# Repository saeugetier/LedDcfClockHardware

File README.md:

# LedDcfClockHardware

The hardware used for https://github.com/saeugetier/LedDcfClock

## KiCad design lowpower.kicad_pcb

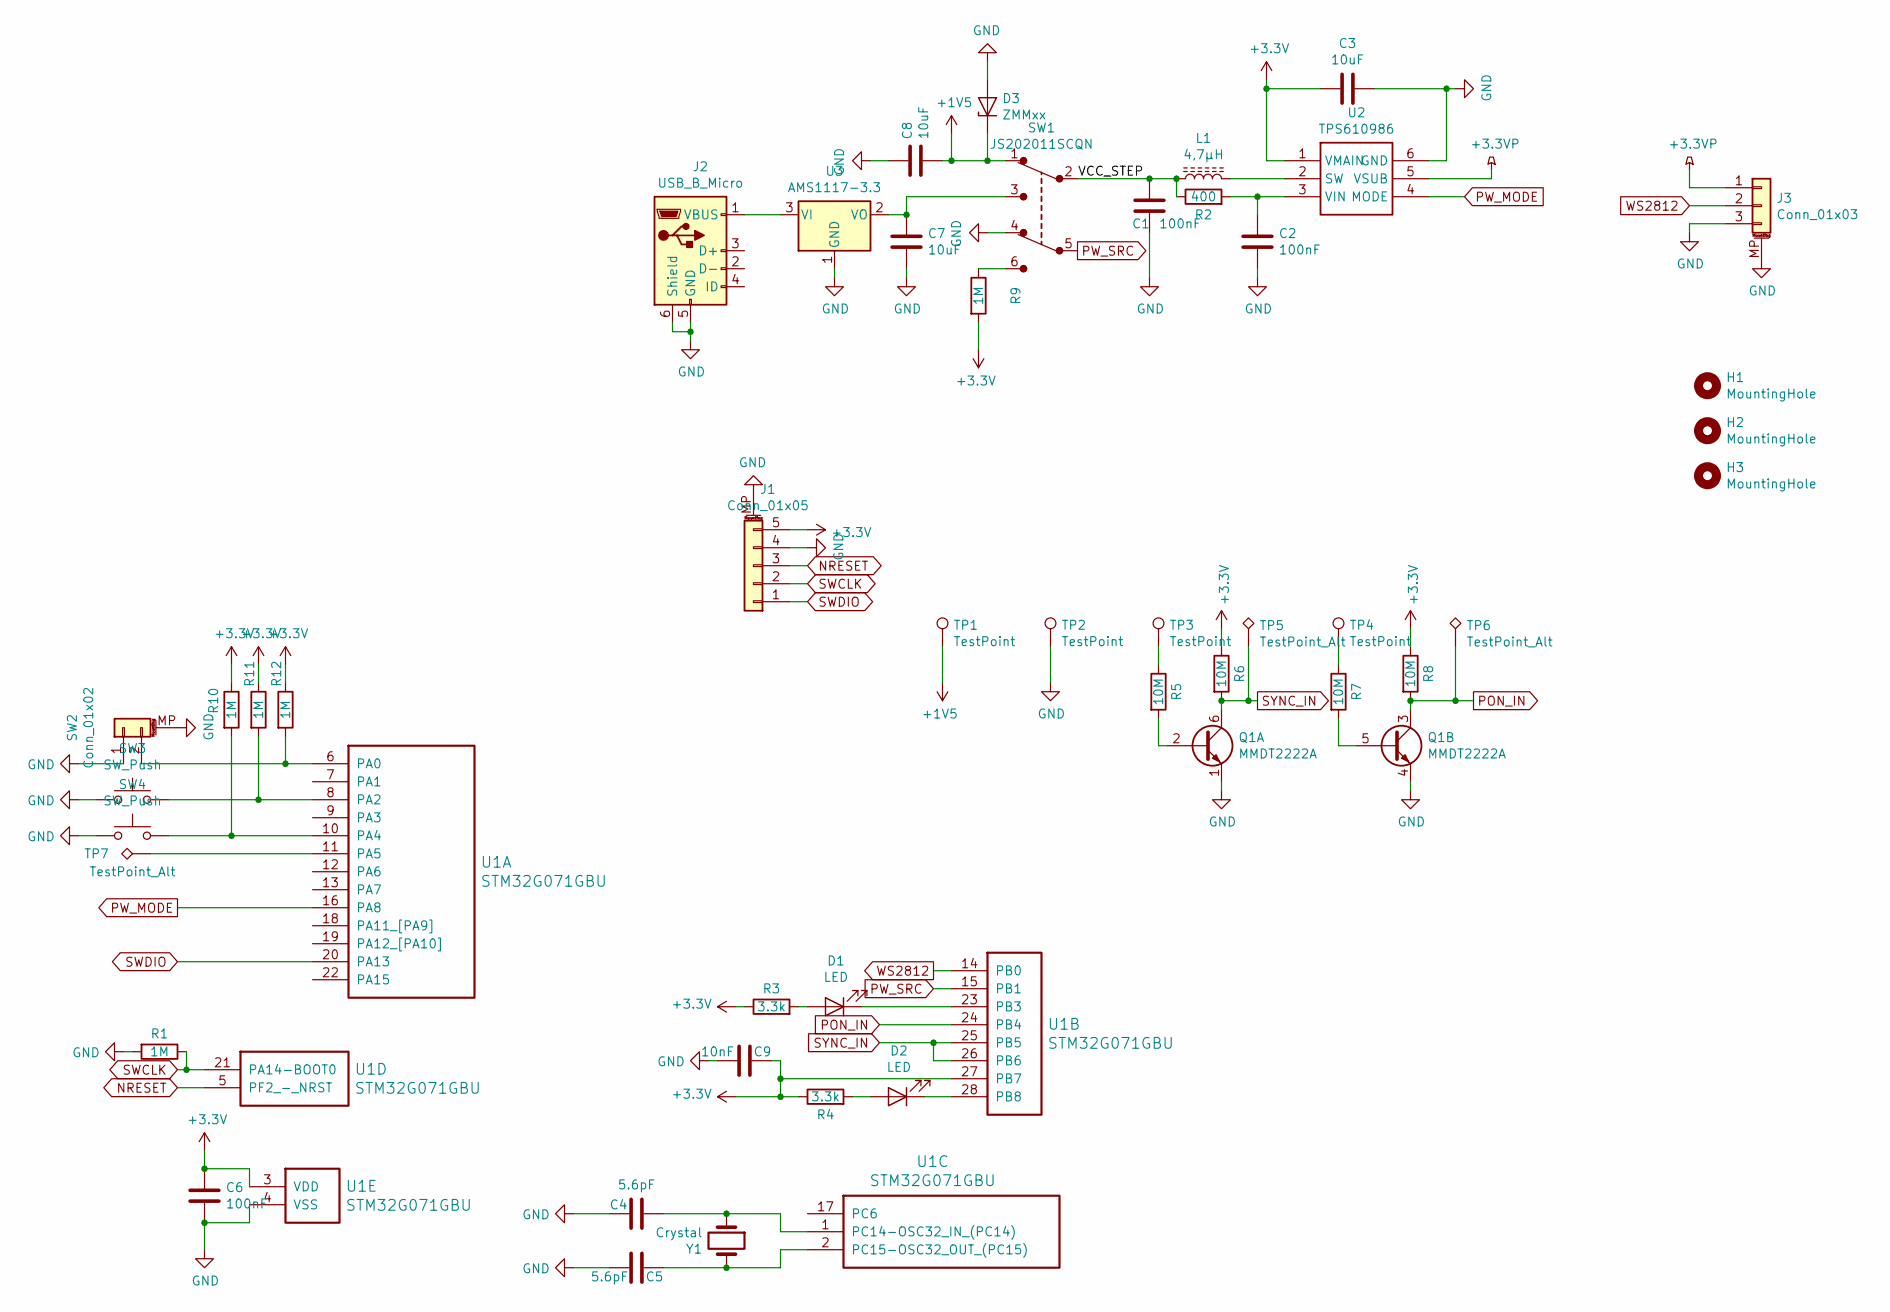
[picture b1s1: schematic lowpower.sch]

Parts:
C1, C2, C6: 100nF; C_0603_1608Metric
C3, C7, C8: 10uF; C_0603_1608Metric
C4, C5: 5.6pF; C_0603_1608Metric
C9: 10nF; C_0603_1608Metric
D1, D2: LED; LED_0603_1608Metric
D3: ZMMxx; D_MiniMELF
H1, H2, H3: MountingHole; MountingHole_3.2mm_M3_DIN965
J1: Conn_01x05; JST_SH_BM05B-SRSS-TB_1x05-1MP_P1.00mm_Vertical
J2: USB_B_Micro; USB_Mini-B_Lumberg_2486_01_Horizontal
J3: Conn_01x03; JST_SH_BM03B-SRSS-TB_1x03-1MP_P1.00mm_Vertical
L1: 4,7µH; VLF302510MT-4R7M
Q1: MMDT2222A; SOT-363_SC-70-6
R1, R9, R10, R11, R12: 1M; R_0603_1608Metric
R2: 400; R_0603_1608Metric
R3, R4: 3.3k; R_0603_1608Metric
R5, R6, R7, R8: 10M; R_0603_1608Metric
SW1: JS202011SCQN; Switch_Slide_JS202011SCQN; MPN JS202011SCQN; Digi-Key_PN 401-2002-1-ND
SW2: Conn_01x02; JST_SH_BM02B-SRSS-TB_1x02-1MP_P1.00mm_Vertical
SW3, SW4: SW_Push; SW_SPST_B3S-1000
TP1, TP2, TP3, TP4: TestPoint; TestPoint_Pad_D2.0mm
TP5, TP6, TP7: TestPoint_Alt; TestPoint_Pad_D1.0mm
U1: STM32G071GBU; QFN-28_4x4mm_P0.5mm
U2: TPS610986; WSON-6_1.5x1.5mm_P0.5mm
U3: AMS1117-3.3; SOT-223-3_TabPin2
Y1: Crystal; Crystal_C38-LF_D3.0mm_L8.0mm_Horizontal

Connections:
+1V5: C8.1, D3.1 (K), SW1.1, TP1.1
+3.3VP: J3.1, U2.5 (VSUB)
+3V3: C3.1, C6.2, C9.1, J1.5, R3.1, R4.1, R6.1, R8.1, R9.2, R10.1, R11.1, R12.1, U1.3 (VDD), U1.27 (PB7), U2.1 (VMAIN)
/VCC_STEP: C1.2, L1.1, R2.1, SW1.2
GND: C1.1, C2.1, C3.2, C4.2, C5.2, C6.1, C7.1, C8.2, C9.2, D3.2 (A), J1.4, J1.MP (MountPin), J2.5 (GND), J2.6 (Shield), J3.3, J3.MP (MountPin), Q1.1 (E1), Q1.4 (E2), R1.2, SW1.4, SW2.1, SW2.MP (MountPin), SW3.1, SW4.1, TP2.1, U1.4 (VSS), U2.6 (GND), U3.1 (GND)
NRESET: J1.3, U1.5 (PF2_-_NRST)
unnamed: C2.2, R2.2, U2.3 (VIN)
unnamed: C4.1, U1.1 (PC14-OSC32_IN_(PC14)), Y1.1
unnamed: C5.1, U1.2 (PC15-OSC32_OUT_(PC15)), Y1.2
unnamed: C7.2, SW1.3, U3.2 (VO)
unnamed: D1.1 (K), U1.23 (PB3)
unnamed: D1.2 (A), R3.2
unnamed: D2.1 (K), U1.28 (PB8)
unnamed: D2.2 (A), R4.2
unnamed: J2.1 (VBUS), U3.3 (VI)
unnamed: L1.2, U2.2 (SW)
unnamed: Q1.2 (B1), R5.2
unnamed: Q1.5 (B2), R7.2
unnamed: R5.1, TP3.1
unnamed: R7.1, TP4.1
unnamed: R9.1, SW1.6
unnamed: R10.2, SW4.2, U1.10 (PA4)
unnamed: R11.2, SW3.2, U1.8 (PA2)
unnamed: R12.2, SW2.2, U1.6 (PA0)
unnamed: TP7.1, U1.11 (PA5)
PON_IN: Q1.3 (C2), R8.2, TP6.1, U1.24 (PB4)
PW_MODE: U1.16 (PA8), U2.4 (MODE)
PW_SRC: SW1.5, U1.15 (PB1)
SWCLK: J1.2, R1.1, U1.21 (PA14-BOOT0)
SWDIO: J1.1, U1.20 (PA13)
SYNC_IN: Q1.6 (C1), R6.2, TP5.1, U1.25 (PB5), U1.26 (PB6)
WS2812: J3.2, U1.14 (PB0)

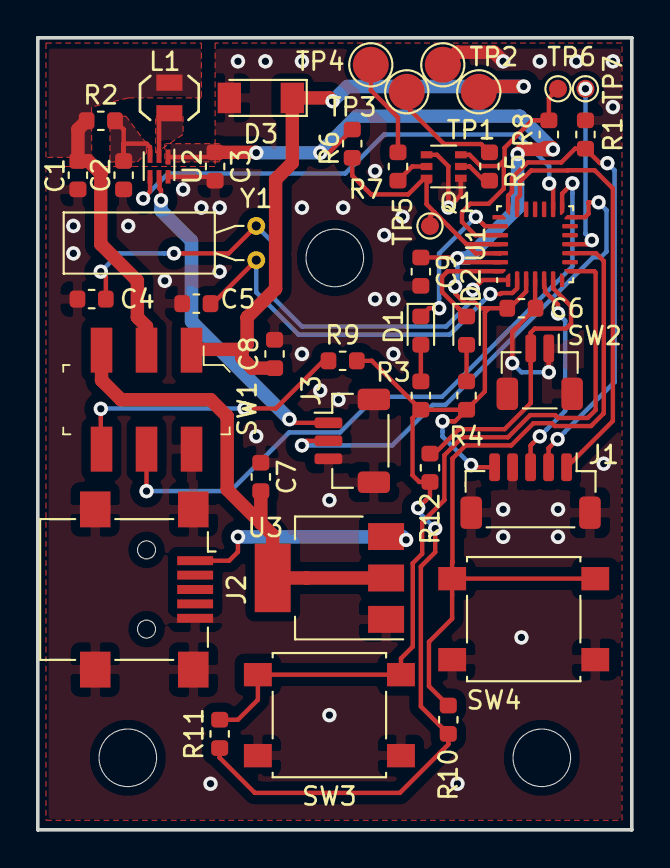
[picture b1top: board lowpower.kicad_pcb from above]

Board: 2 copper layers, 33.0 x 44.0 mm, 47 parts (0 on the bottom side), 32 nets.

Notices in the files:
parts and their libraries:
Copyright 2016 Accelerated Designs. All rights reserved.
